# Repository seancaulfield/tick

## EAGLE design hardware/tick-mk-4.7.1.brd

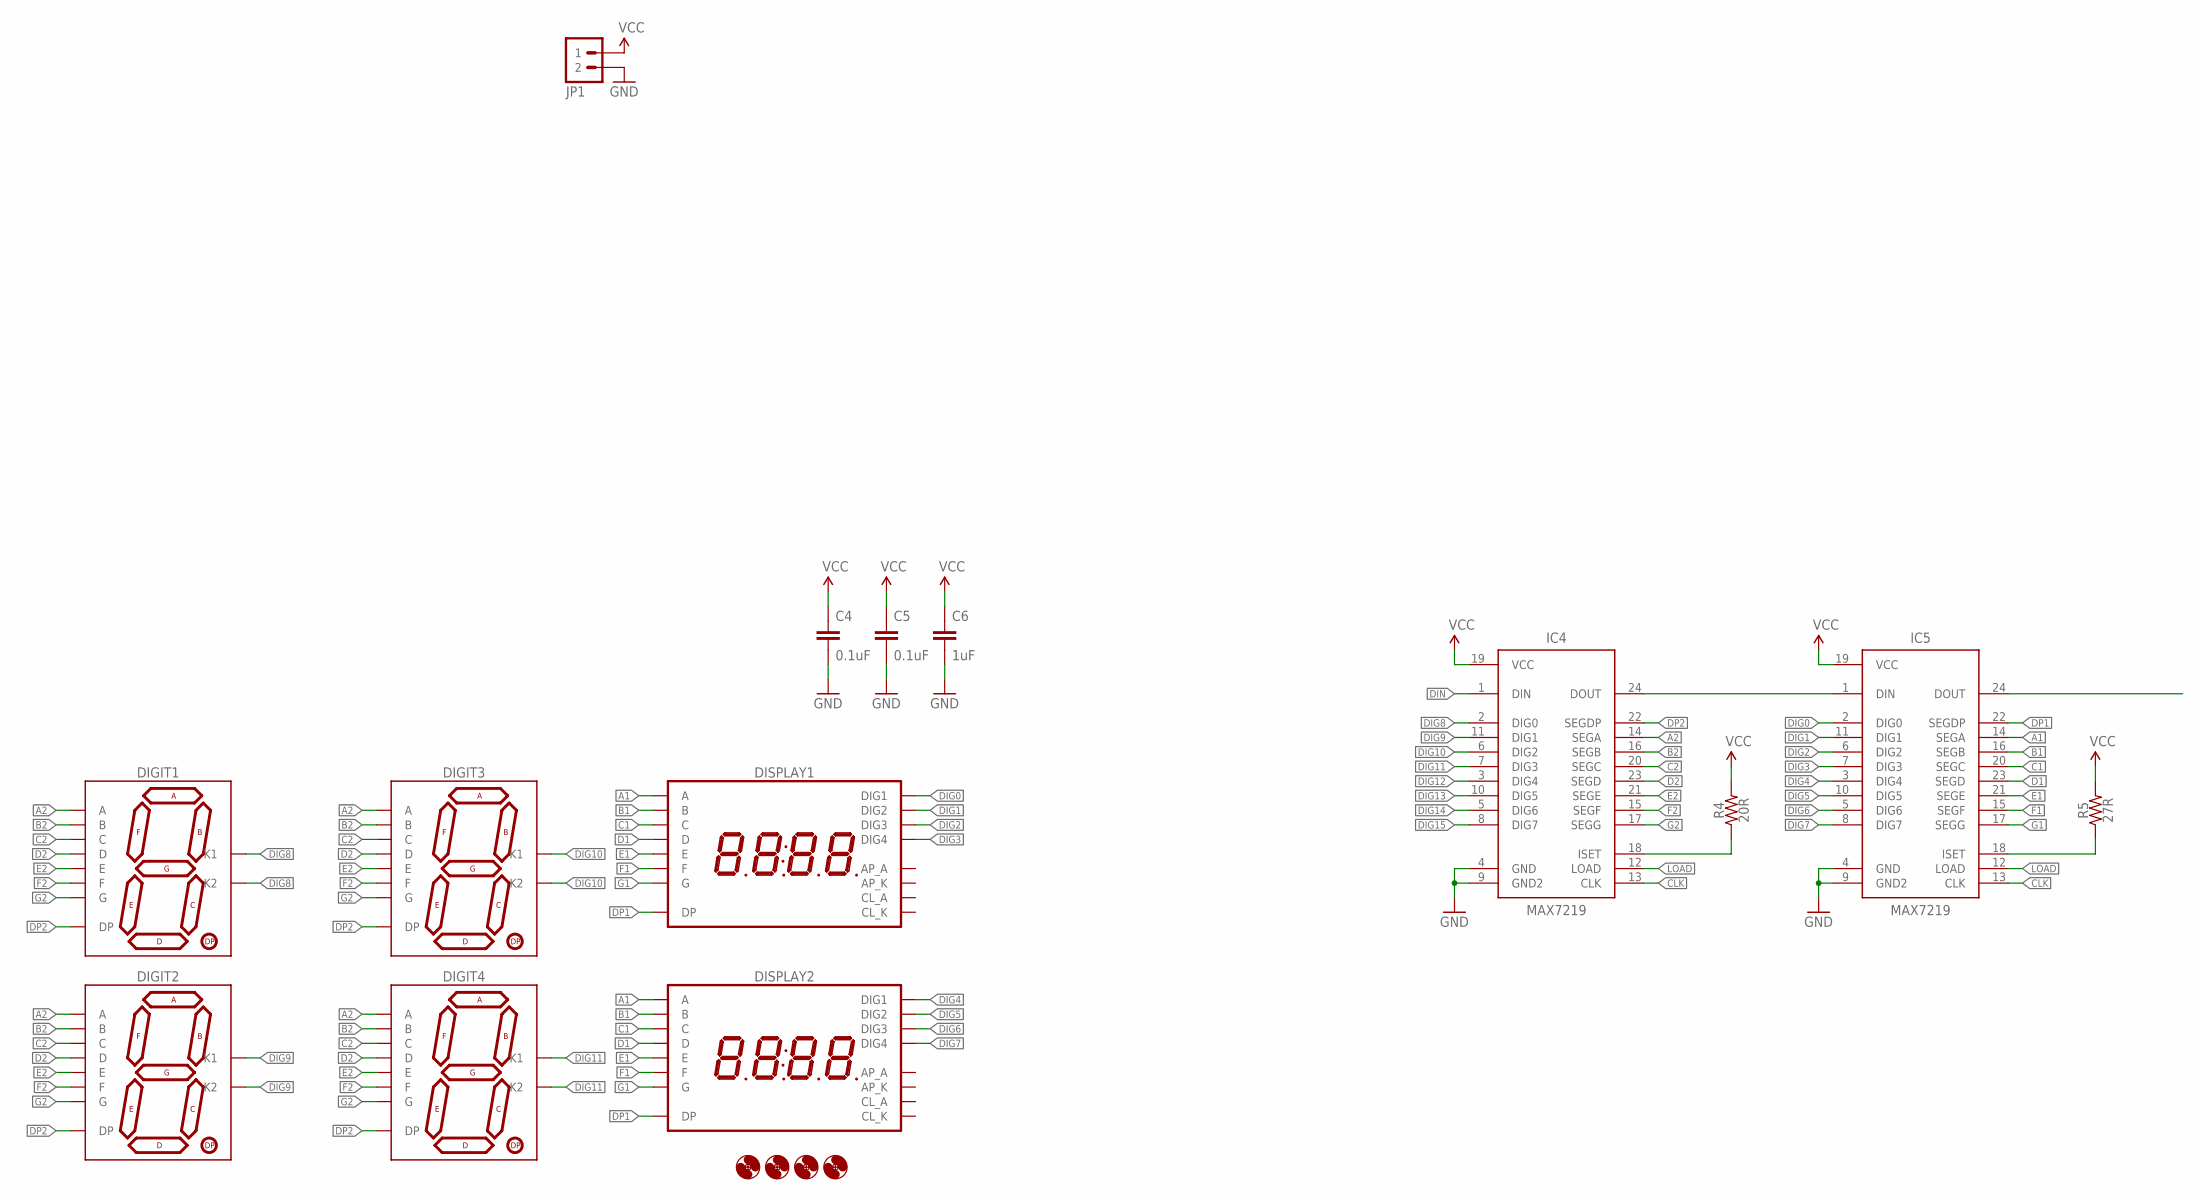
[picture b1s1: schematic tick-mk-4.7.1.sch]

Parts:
C4, C5: 0.1uF; C025-024X044
C6: 1uF; C025-024X044
DIGIT1, DIGIT2, DIGIT3, DIGIT4: 7SEG_1DIGPTH-25.4MM-BARE; 7SEG_1DIG_25.4MM_NOSILK
DISPLAY1, DISPLAY2: 7SEG_4DIGIT_COLON_APOS; 7SEG_4DIG_10MM
H1, H2, H3, H4: HOLE#2; HOLE-#2
IC4, IC5: MAX7219; SO24W
JP1: M02JST-XH-VERT; JST-2-XH-VERT-PTH
R4: 20R; RESISTOR-AXIAL-PTH-7.62MM
R5: 27R; RESISTOR-AXIAL-PTH-7.62MM

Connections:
A1: DISPLAY1.14 (A), DISPLAY2.14 (A), IC5.14 (SEGA)
A2: DIGIT1.7 (A), DIGIT2.7 (A), DIGIT3.7 (A), DIGIT4.7 (A), IC4.14 (SEGA)
B1: DISPLAY1.16 (B), DISPLAY2.16 (B), IC5.16 (SEGB)
B2: DIGIT1.6 (B), DIGIT2.6 (B), DIGIT3.6 (B), DIGIT4.6 (B), IC4.16 (SEGB)
C1: DISPLAY1.13 (C), DISPLAY2.13 (C), IC5.20 (SEGC)
C2: DIGIT1.4 (C), DIGIT2.4 (C), DIGIT3.4 (C), DIGIT4.4 (C), IC4.20 (SEGC)
CLK: IC4.13 (CLK), IC5.13 (CLK)
D1: DISPLAY1.3 (D), DISPLAY2.3 (D), IC5.23 (SEGD)
D2: DIGIT1.2 (D), DIGIT2.2 (D), DIGIT3.2 (D), DIGIT4.2 (D), IC4.23 (SEGD)
DIG0: DISPLAY1.1 (DIG1), IC5.2 (DIG0)
DIG1: DISPLAY1.2 (DIG2), IC5.11 (DIG1)
DIG2: DISPLAY1.6 (DIG3), IC5.6 (DIG2)
DIG3: DISPLAY1.8 (DIG4), IC5.7 (DIG3)
DIG4: DISPLAY2.1 (DIG1), IC5.3 (DIG4)
DIG5: DISPLAY2.2 (DIG2), IC5.10 (DIG5)
DIG6: DISPLAY2.6 (DIG3), IC5.5 (DIG6)
DIG7: DISPLAY2.8 (DIG4), IC5.8 (DIG7)
DIG8: DIGIT1.3 (K1), DIGIT1.8 (K2), IC4.2 (DIG0)
DIG9: DIGIT2.3 (K1), DIGIT2.8 (K2), IC4.11 (DIG1)
DIG10: DIGIT3.3 (K1), DIGIT3.8 (K2), IC4.6 (DIG2)
DIG11: DIGIT4.3 (K1), DIGIT4.8 (K2), IC4.7 (DIG3)
DIG12: IC4.3 (DIG4)
DIG13: IC4.10 (DIG5)
DIG14: IC4.5 (DIG6)
DIG15: IC4.8 (DIG7)
DIN: IC4.1 (DIN)
DOUT: IC4.24 (DOUT), IC5.1 (DIN)
DP1: DISPLAY1.7 (DP), DISPLAY2.7 (DP), IC5.22 (SEGDP)
DP2: DIGIT1.5 (DP), DIGIT2.5 (DP), DIGIT3.5 (DP), DIGIT4.5 (DP), IC4.22 (SEGDP)
E1: DISPLAY1.5 (E), DISPLAY2.5 (E), IC5.21 (SEGE)
E2: DIGIT1.1 (E), DIGIT2.1 (E), DIGIT3.1 (E), DIGIT4.1 (E), IC4.21 (SEGE)
F1: DISPLAY1.11 (F), DISPLAY2.11 (F), IC5.15 (SEGF)
F2: DIGIT1.9 (F), DIGIT2.9 (F), DIGIT3.9 (F), DIGIT4.9 (F), IC4.15 (SEGF)
G1: DISPLAY1.15 (G), DISPLAY2.15 (G), IC5.17 (SEGG)
G2: DIGIT1.10 (G), DIGIT2.10 (G), DIGIT3.10 (G), DIGIT4.10 (G), IC4.17 (SEGG)
GND: C4.2, C5.2, C6.2, IC4.4 (GND), IC4.9 (GND2), IC5.4 (GND), IC5.9 (GND2), JP1.2
LOAD: IC4.12 (LOAD), IC5.12 (LOAD)
unnamed: IC5.18 (ISET), R5.P$1 (1)
unnamed: IC4.18 (ISET), R4.P$1 (1)
VCC: C4.1, C5.1, C6.1, IC4.19 (VCC), IC5.19 (VCC), JP1.1, R4.P$2 (2), R5.P$2 (2)

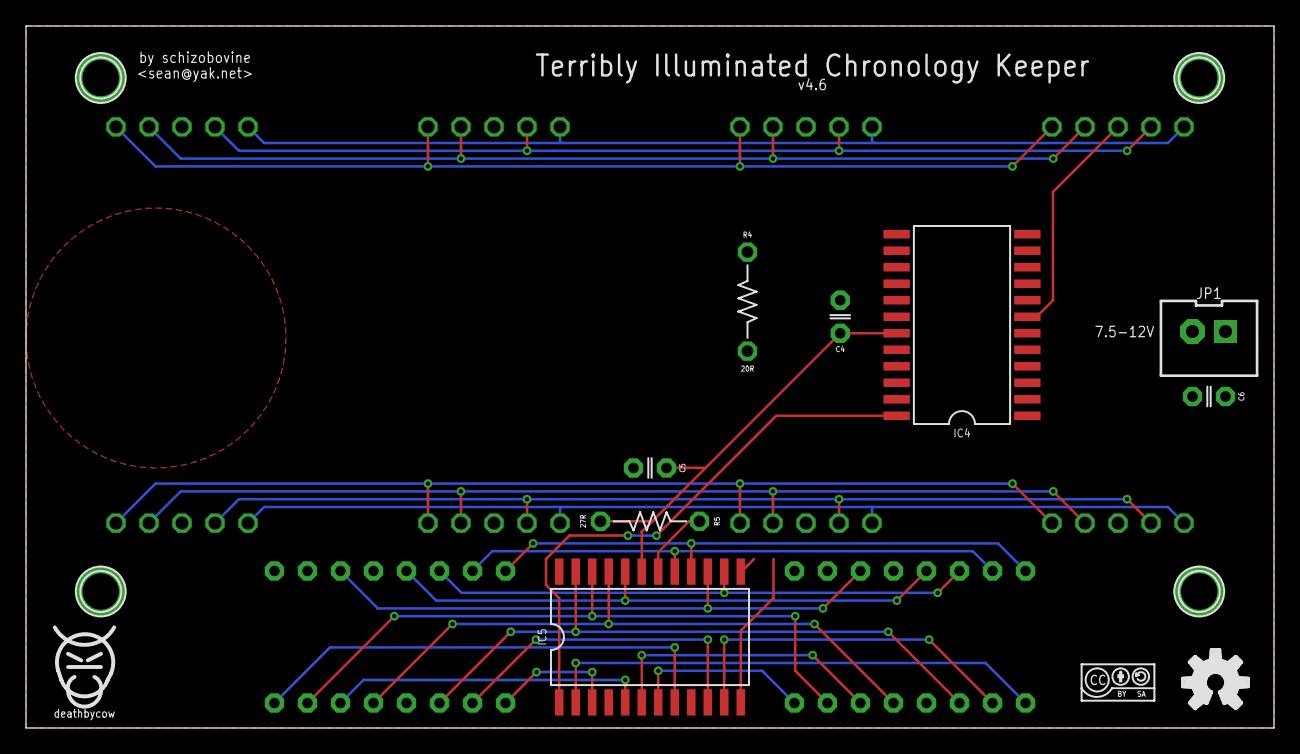
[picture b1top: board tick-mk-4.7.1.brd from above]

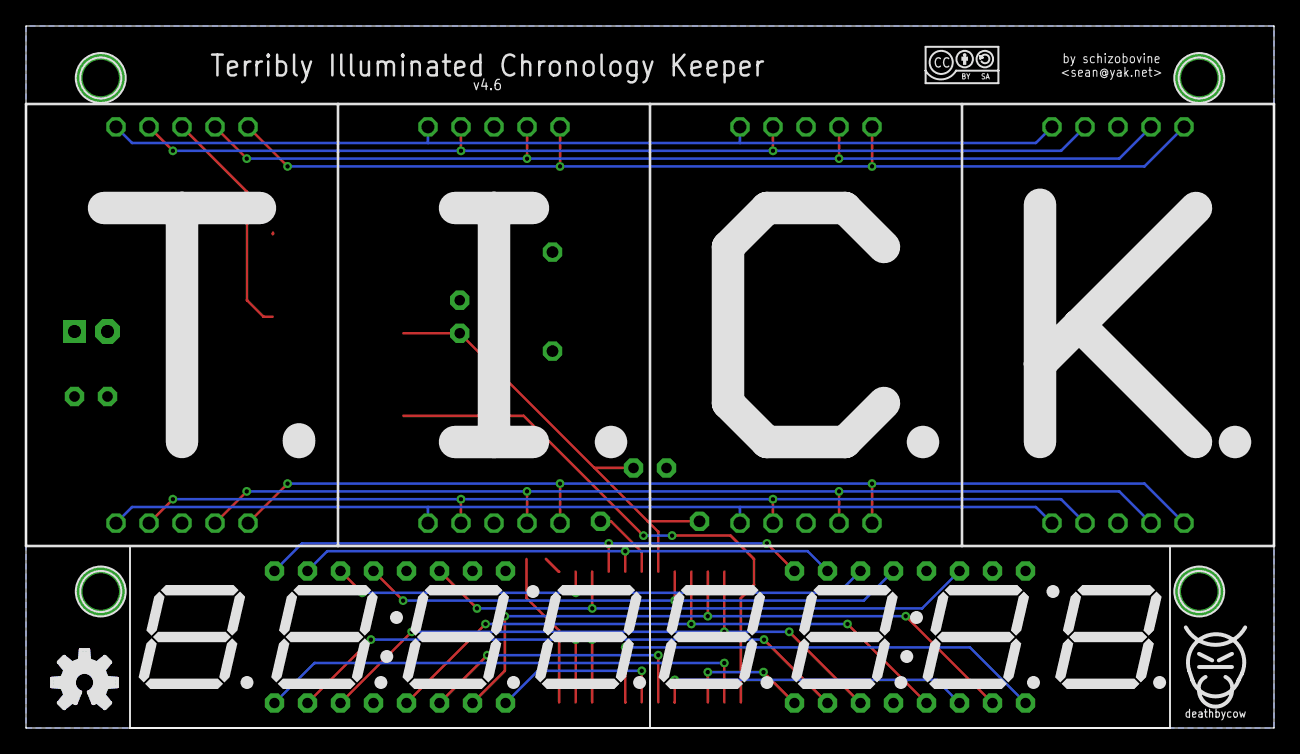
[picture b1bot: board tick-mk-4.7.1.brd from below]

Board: 2 copper layers, 96.0 x 54.0 mm, 24 parts (9 on the bottom side), 35 nets.

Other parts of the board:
U$1, U$4: COW_SMALL
U$2, U$3: CC-BY-SA-4.0-NO-URL
U$5, U$8: OSHWLOGO_TOP_0.2

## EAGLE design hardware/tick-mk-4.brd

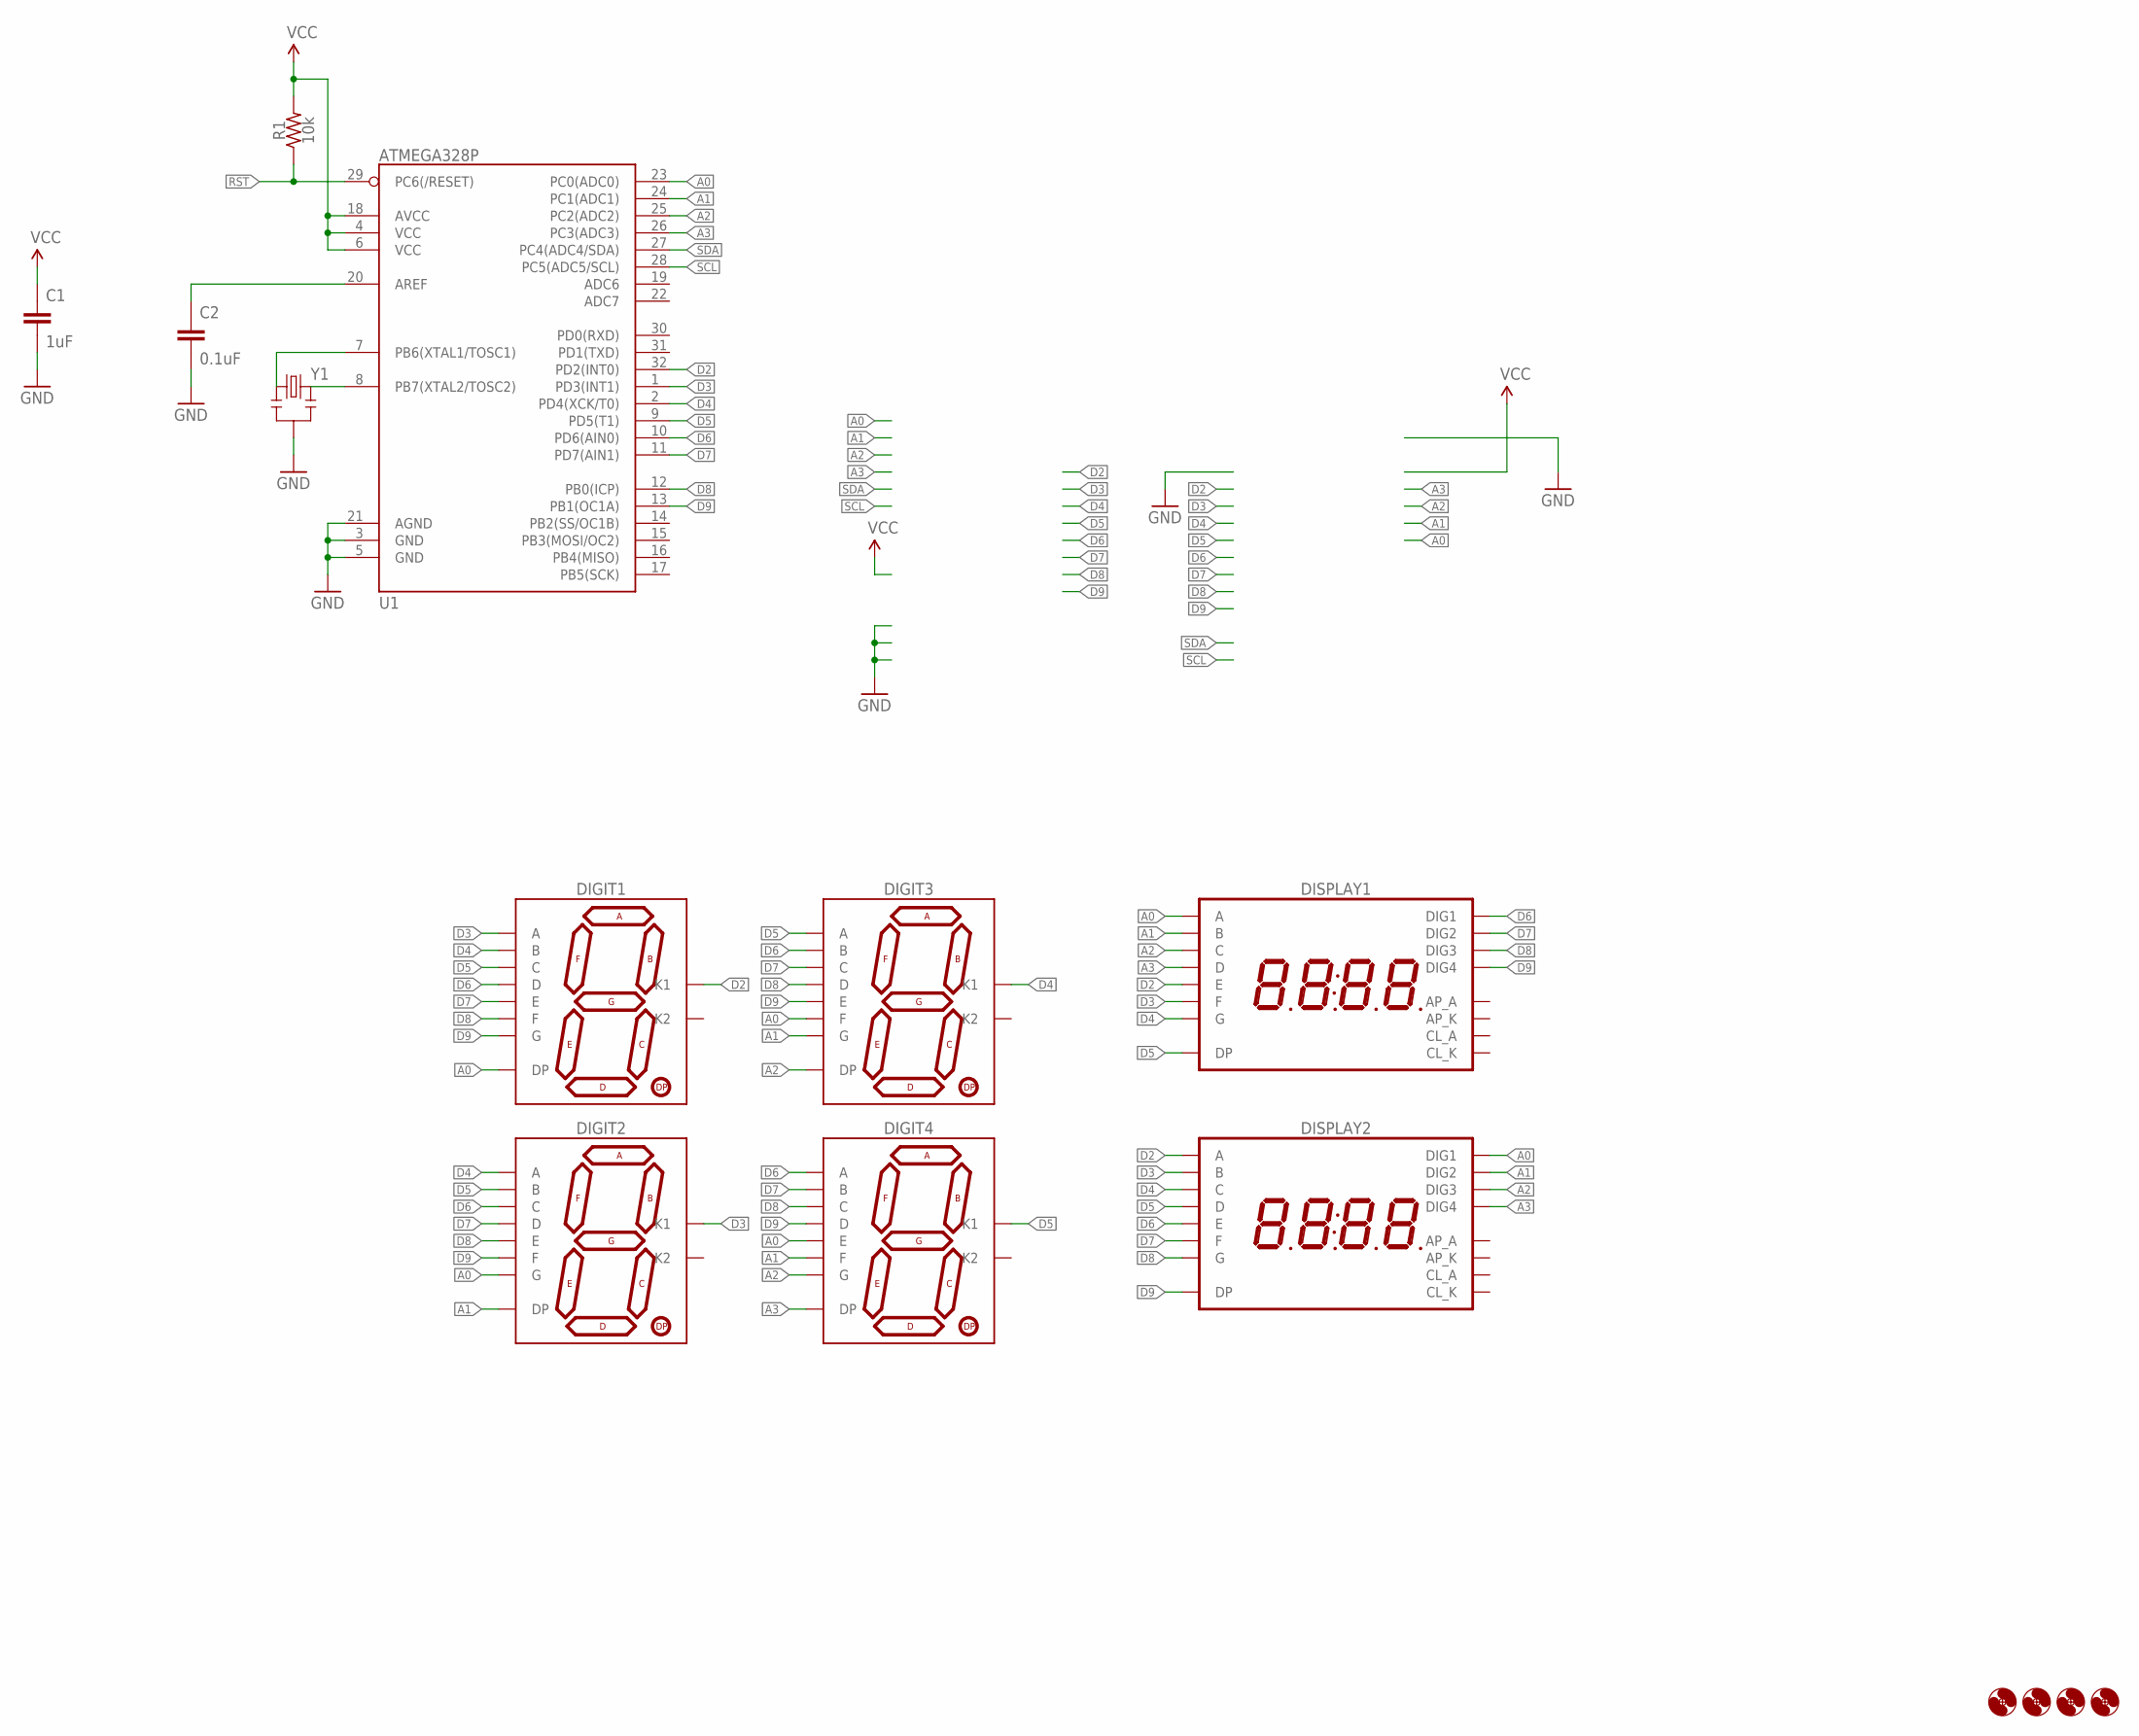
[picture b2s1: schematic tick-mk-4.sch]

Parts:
C1: 1uF; C0805
C2: 0.1uF; C0805
DIGIT1, DIGIT2, DIGIT3, DIGIT4: 7SEG_1DIGPTH-25.4MM; 7SEG_1DIG_25.4MM
DISPLAY1, DISPLAY2: 7SEG_4DIGIT_COLON_APOS; 7SEG_4DIG_10MM
H1, H2, H3, H4: HOLE#2; HOLE-#2
R1: 10k; R0805
U1: ATMEGA328P; TQFP32-08
Y1: RESONATORSMD-4.7X4.1X1.2; RESONATOR-4.7X4.1X1.2MM

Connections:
A0: DIGIT1.5 (DP), DIGIT2.10 (G), DIGIT3.9 (F), DIGIT4.1 (E), DISPLAY1.14 (A), DISPLAY2.1 (DIG1), U1.23 (PC0(ADC0))
A1: DIGIT2.5 (DP), DIGIT3.10 (G), DIGIT4.9 (F), DISPLAY1.16 (B), DISPLAY2.2 (DIG2), U1.24 (PC1(ADC1))
A2: DIGIT3.5 (DP), DIGIT4.10 (G), DISPLAY1.13 (C), DISPLAY2.6 (DIG3), U1.25 (PC2(ADC2))
A3: DIGIT4.5 (DP), DISPLAY1.3 (D), DISPLAY2.8 (DIG4), U1.26 (PC3(ADC3))
D2: DIGIT1.3 (K1), DISPLAY1.5 (E), DISPLAY2.14 (A), U1.32 (PD2(INT0))
D3: DIGIT1.7 (A), DIGIT2.3 (K1), DISPLAY1.11 (F), DISPLAY2.16 (B), U1.1 (PD3(INT1))
D4: DIGIT1.6 (B), DIGIT2.7 (A), DIGIT3.3 (K1), DISPLAY1.15 (G), DISPLAY2.13 (C), U1.2 (PD4(XCK/T0))
D5: DIGIT1.4 (C), DIGIT2.6 (B), DIGIT3.7 (A), DIGIT4.3 (K1), DISPLAY1.7 (DP), DISPLAY2.3 (D), U1.9 (PD5(T1))
D6: DIGIT1.2 (D), DIGIT2.4 (C), DIGIT3.6 (B), DIGIT4.7 (A), DISPLAY1.1 (DIG1), DISPLAY2.5 (E), U1.10 (PD6(AIN0))
D7: DIGIT1.1 (E), DIGIT2.2 (D), DIGIT3.4 (C), DIGIT4.6 (B), DISPLAY1.2 (DIG2), DISPLAY2.11 (F), U1.11 (PD7(AIN1))
D8: DIGIT1.9 (F), DIGIT2.1 (E), DIGIT3.2 (D), DIGIT4.4 (C), DISPLAY1.6 (DIG3), DISPLAY2.15 (G), U1.12 (PB0(ICP))
D9: DIGIT1.10 (G), DIGIT2.9 (F), DIGIT3.1 (E), DIGIT4.2 (D), DISPLAY1.8 (DIG4), DISPLAY2.7 (DP), U1.13 (PB1(OC1A))
GND: C1.2, C2.2, U1.3 (GND), U1.5 (GND), U1.21 (AGND), Y1.2
unnamed: C2.1, U1.20 (AREF)
unnamed: U1.7 (PB6(XTAL1/TOSC1)), Y1.1
unnamed: U1.8 (PB7(XTAL2/TOSC2)), Y1.3
RST: R1.1, U1.29 (PC6(/RESET))
SCL: U1.28 (PC5(ADC5/SCL))
SDA: U1.27 (PC4(ADC4/SDA))
VCC: C1.1, R1.2, U1.4 (VCC), U1.6 (VCC), U1.18 (AVCC)

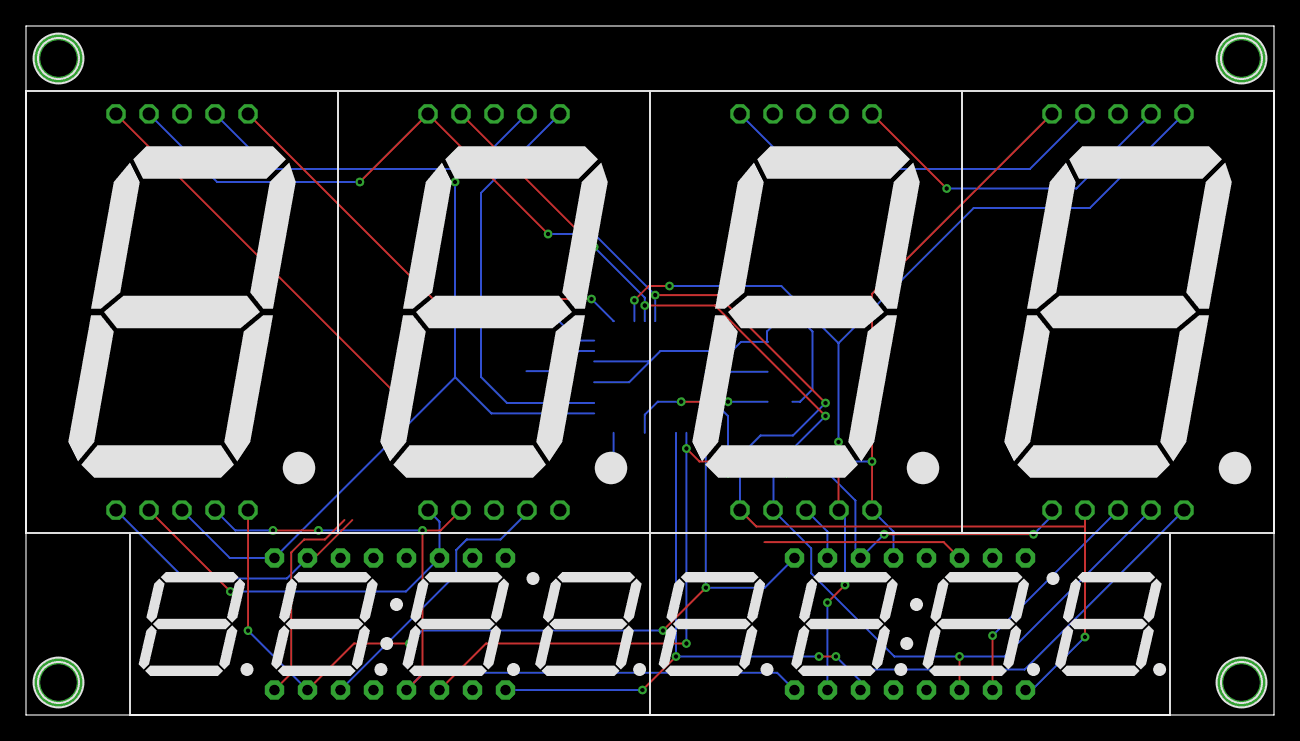
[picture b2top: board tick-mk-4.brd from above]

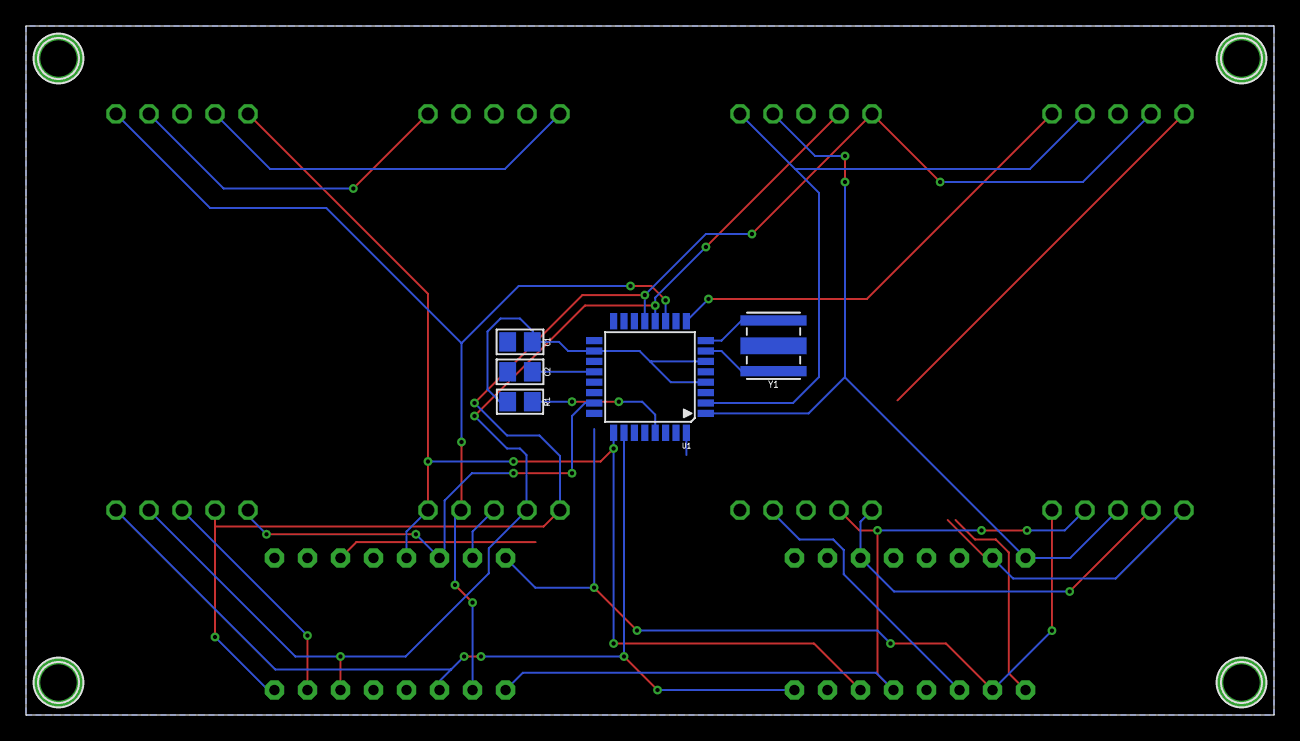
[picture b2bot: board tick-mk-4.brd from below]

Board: 2 copper layers, 96.0 x 53.0 mm, 15 parts (5 on the bottom side), 18 nets.

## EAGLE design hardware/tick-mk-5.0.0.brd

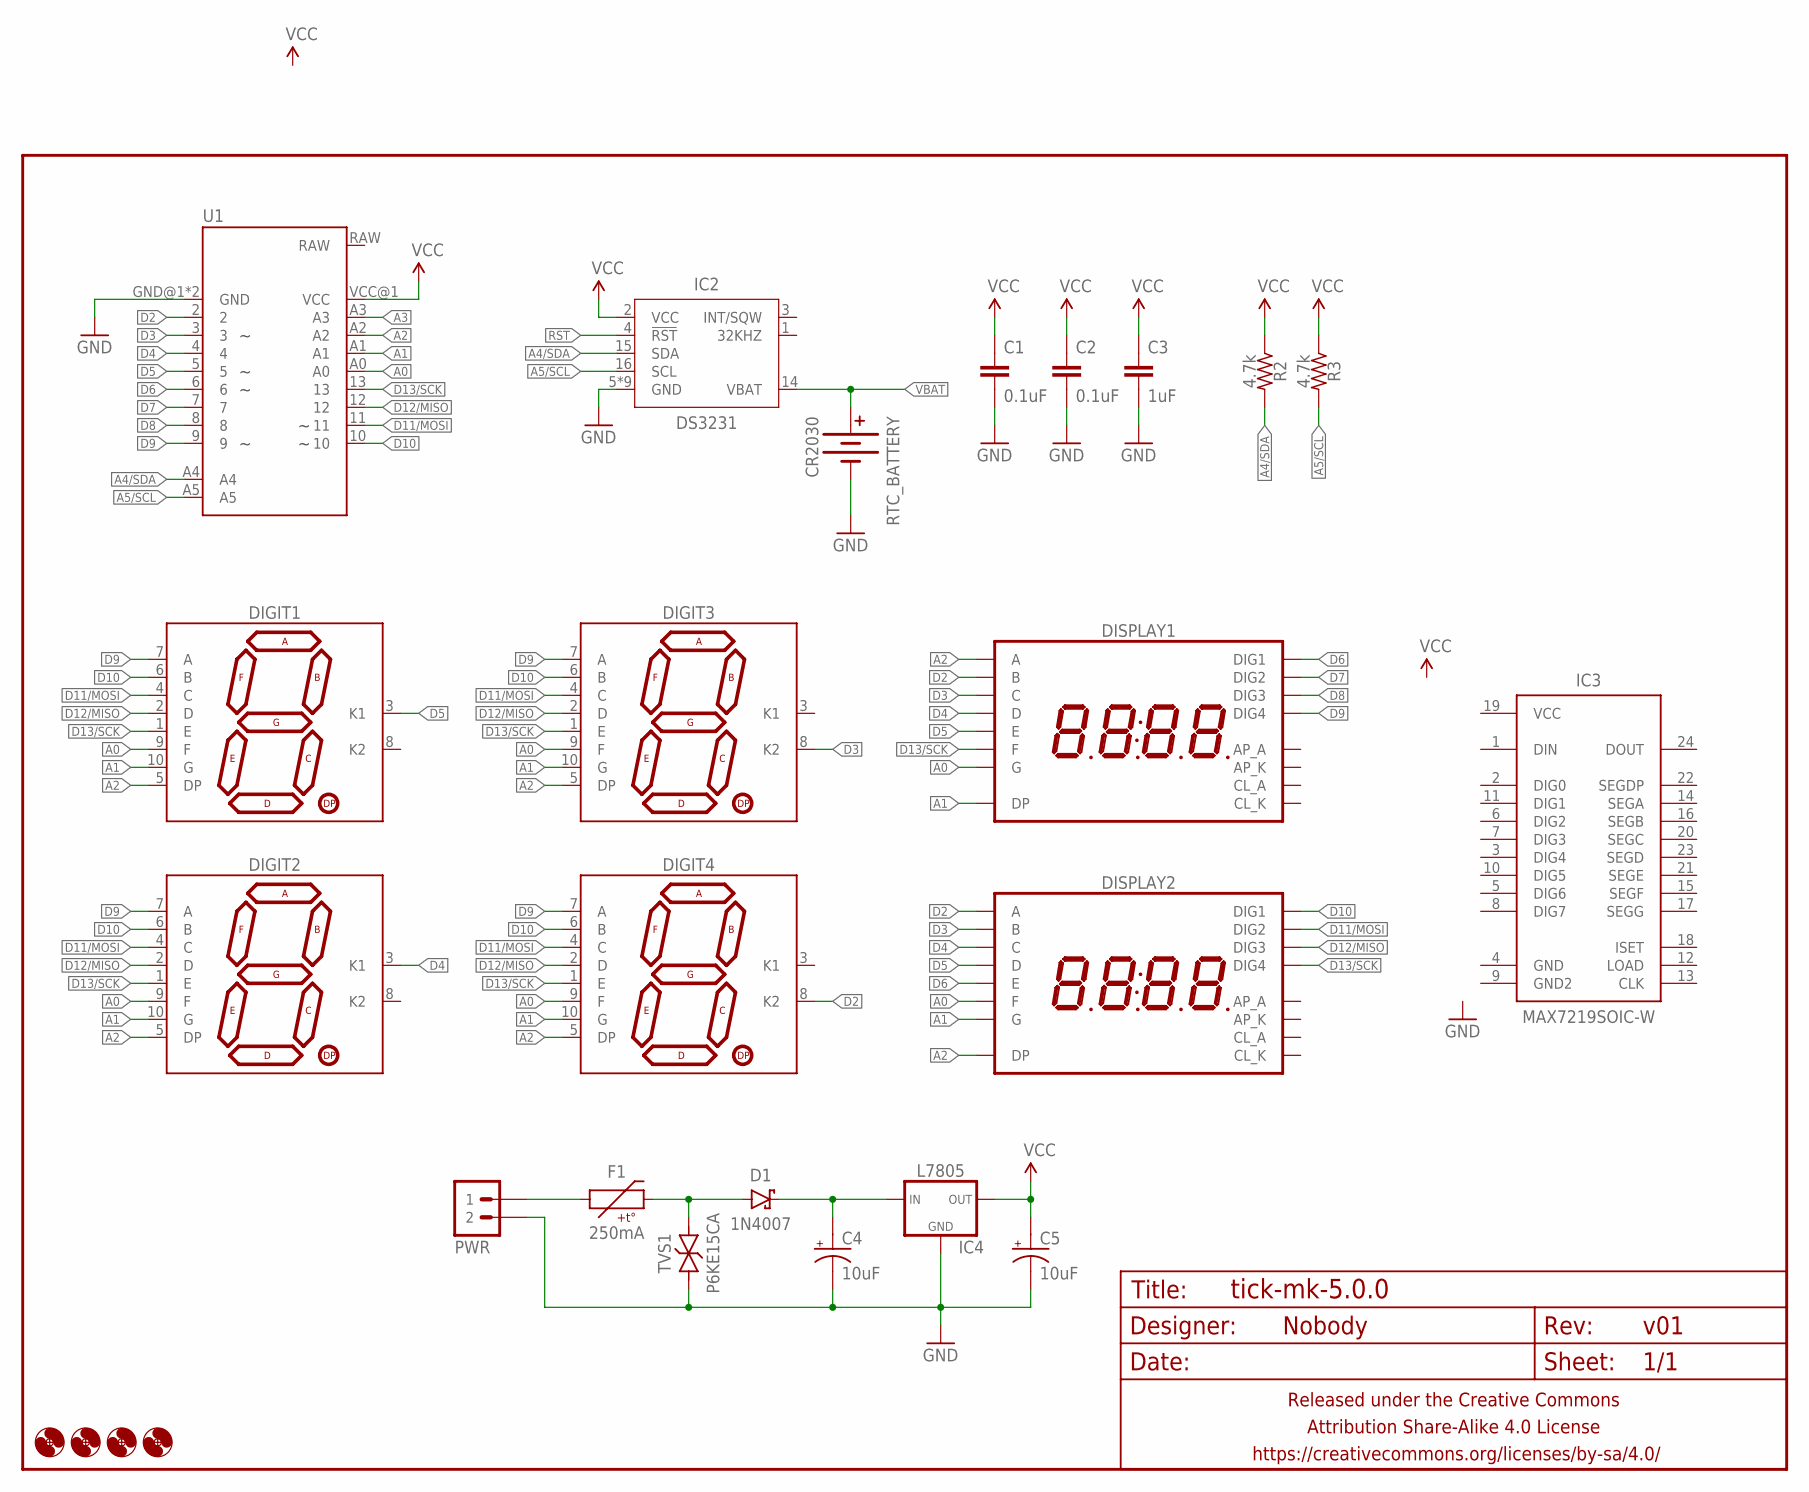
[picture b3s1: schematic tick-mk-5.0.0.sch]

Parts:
C1, C2: 0.1uF; C025-024X044
C3: 1uF; C025-024X044
C4, C5: 10uF; E2-5
D1: 1N4007; DIODE-10.16MM
DIGIT1, DIGIT2, DIGIT3, DIGIT4: 7SEG_1DIGPTH-25.4MM-BARE; 7SEG_1DIG_25.4MM_NOSILK
DISPLAY1, DISPLAY2: 7SEG_4DIGIT_COLON_APOS; 7SEG_4DIG_10MM
F1: 250mA; PTC-PTH-5.08MM
FRAME1: FRAME-LETTERNO_PACKAGE; DUMMY
H1, H2, H3, H4: HOLE2,5; 2,5
IC2: DS3231; SO16W
IC3: MAX7219SOIC-W; SO24W
IC4: L7805; TO220-IGO-THERMPAD
PWR: M02JST-PTH-VERT; JST-2-PH-VERT-PTH
R2, R3: 4.7k; RESISTOR-AXIAL-PTH-6.35MM
RTC_BATTERY: CR2030; BATTCON_20MM_MINE_STAHPIT
TVS1: P6KE15CA; DO-41-TVS-BI-10.16MM
U1: ARDUINO_PRO_MINI_TICK2

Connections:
A0: DIGIT1.9 (F), DIGIT2.9 (F), DIGIT3.9 (F), DIGIT4.9 (F), DISPLAY1.15 (G), DISPLAY2.11 (F), U1.A0
A1: DIGIT1.10 (G), DIGIT2.10 (G), DIGIT3.10 (G), DIGIT4.10 (G), DISPLAY1.7 (DP), DISPLAY2.15 (G), U1.A1
A2: DIGIT1.5 (DP), DIGIT2.5 (DP), DIGIT3.5 (DP), DIGIT4.5 (DP), DISPLAY1.14 (A), DISPLAY2.7 (DP), U1.A2
A3: U1.A3
A4/SDA: IC2.15 (SDA), R2.P$2 (2), U1.A4
A5/SCL: IC2.16 (SCL), R3.P$2 (2), U1.A5
D2: DIGIT4.8 (K2), DISPLAY1.16 (B), DISPLAY2.14 (A), U1.2
D3: DIGIT3.8 (K2), DISPLAY1.13 (C), DISPLAY2.16 (B), U1.3
D4: DIGIT2.3 (K1), DISPLAY1.3 (D), DISPLAY2.13 (C), U1.4
D5: DIGIT1.3 (K1), DISPLAY1.5 (E), DISPLAY2.3 (D), U1.5
D6: DISPLAY1.1 (DIG1), DISPLAY2.5 (E), U1.6
D7: DISPLAY1.2 (DIG2), U1.7
D8: DISPLAY1.6 (DIG3), U1.8
D9: DIGIT1.7 (A), DIGIT2.7 (A), DIGIT3.7 (A), DIGIT4.7 (A), DISPLAY1.8 (DIG4), U1.9
D10: DIGIT1.6 (B), DIGIT2.6 (B), DIGIT3.6 (B), DIGIT4.6 (B), DISPLAY2.1 (DIG1), U1.10
D11/MOSI: DIGIT1.4 (C), DIGIT2.4 (C), DIGIT3.4 (C), DIGIT4.4 (C), DISPLAY2.2 (DIG2), U1.11
D12/MISO: DIGIT1.2 (D), DIGIT2.2 (D), DIGIT3.2 (D), DIGIT4.2 (D), DISPLAY2.6 (DIG3), U1.12
D13/SCK: DIGIT1.1 (E), DIGIT2.1 (E), DIGIT3.1 (E), DIGIT4.1 (E), DISPLAY1.11 (F), DISPLAY2.8 (DIG4), U1.13
GND: C1.2, C2.2, C3.2, C4.-, C5.-, IC2.5 (GND), IC2.6 (GND), IC2.7 (GND), IC2.8 (GND), IC2.9 (GND), IC2.10 (GND), IC2.11 (GND), IC2.12 (GND), IC2.13 (GND), IC4.4 (GND), IC4.GND, PWR.2, RTC_BATTERY.BOTTOM (-), TVS1.P$1 (1), U1.GND@1 (GND), U1.GND@2 (GND)
unnamed: D1.A, F1.P$2 (2), TVS1.P$2 (2)
unnamed: F1.P$1 (1), PWR.1
unnamed: C4.+, D1.C, IC4.IN
RST: IC2.4 (!RST)
VBAT: IC2.14 (VBAT), RTC_BATTERY.TOP@1 (+), RTC_BATTERY.TOP@2 (+)
VCC: C1.1, C2.1, C3.1, C5.+, IC2.2 (VCC), IC4.OUT, R2.P$1 (1), R3.P$1 (1), U1.VCC@1 (VCC)

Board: 2 copper layers, 28 parts (7 on the bottom side), 23 nets, no tracks yet.

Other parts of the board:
U$1: TICK_SYMBOL

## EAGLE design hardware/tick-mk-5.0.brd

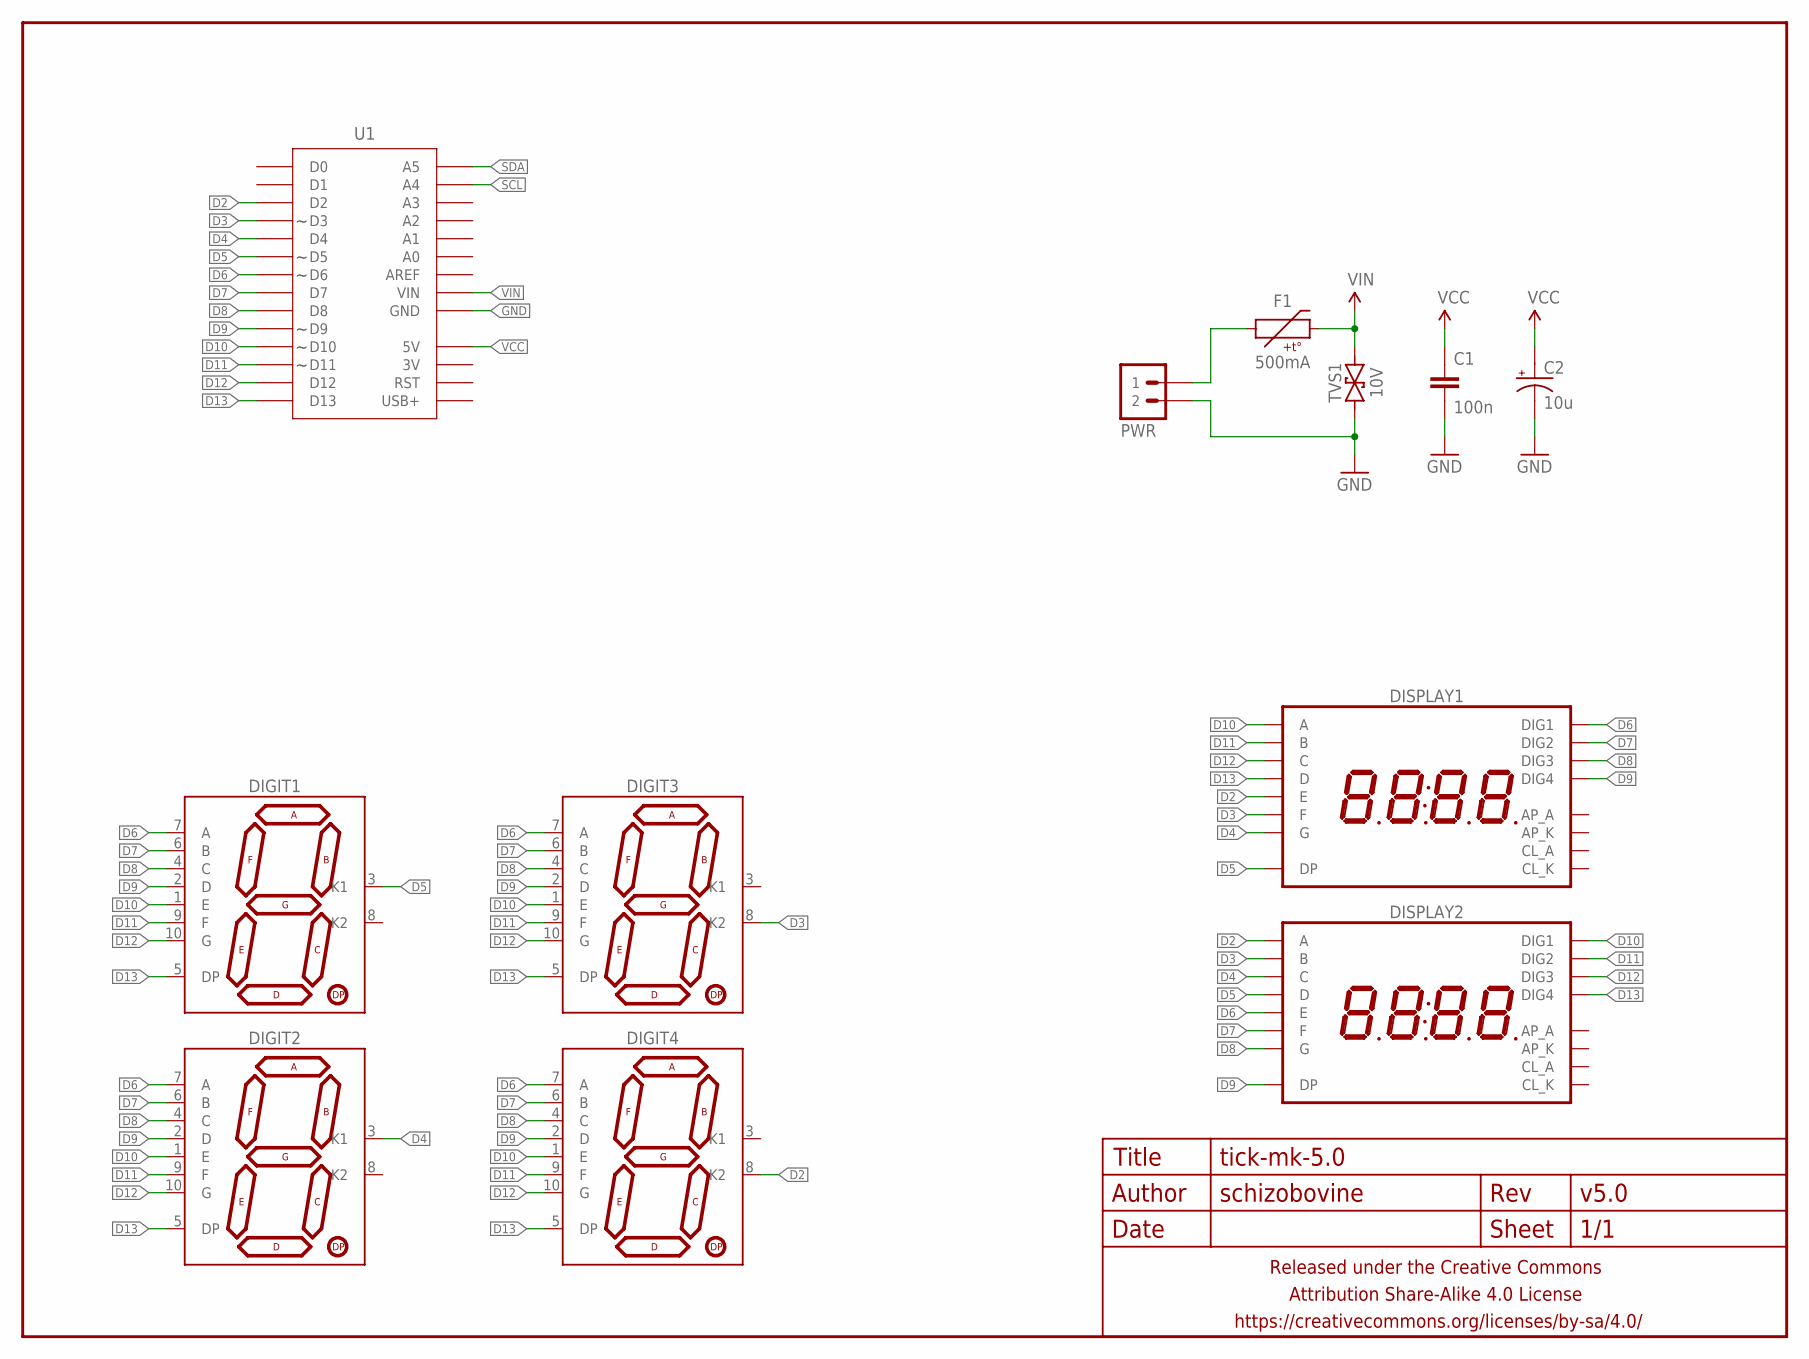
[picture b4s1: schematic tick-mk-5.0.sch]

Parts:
C1: 100n; C025-024X044
C2: 10u; E2-5
DIGIT1, DIGIT2, DIGIT3, DIGIT4: 7SEG_1DIGPTH-25.4MM-BARE; 7SEG_1DIG_25.4MM_NOSILK
DISPLAY1, DISPLAY2: 7SEG_4DIGIT_COLON_APOS; 7SEG_4DIG_10MM
F1: 500mA; PTC-PTH-5.08MM
FRAME1: FRAME-LETTERNO_PACKAGE; DUMMY
PWR: M02JST-PTH-VERT; JST-2-PH-VERT-PTH
TVS1: 10V; DO-41-TVS-BI-10.16MM
U1: ADAFRUIT_METRO_MININOHOLES-NOOUTLINE-SILK; ADAFRUIT_METRO_MINI

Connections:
D2: DIGIT4.8 (K2), DISPLAY1.5 (E), DISPLAY2.14 (A), U1.3 (D2)
D3: DIGIT3.8 (K2), DISPLAY1.11 (F), DISPLAY2.16 (B), U1.4 (D3)
D4: DIGIT2.3 (K1), DISPLAY1.15 (G), DISPLAY2.13 (C), U1.5 (D4)
D5: DIGIT1.3 (K1), DISPLAY1.7 (DP), DISPLAY2.3 (D), U1.6 (D5)
D6: DIGIT1.7 (A), DIGIT2.7 (A), DIGIT3.7 (A), DIGIT4.7 (A), DISPLAY1.1 (DIG1), DISPLAY2.5 (E), U1.7 (D6)
D7: DIGIT1.6 (B), DIGIT2.6 (B), DIGIT3.6 (B), DIGIT4.6 (B), DISPLAY1.2 (DIG2), DISPLAY2.11 (F), U1.8 (D7)
D8: DIGIT1.4 (C), DIGIT2.4 (C), DIGIT3.4 (C), DIGIT4.4 (C), DISPLAY1.6 (DIG3), DISPLAY2.15 (G), U1.9 (D8)
D9: DIGIT1.2 (D), DIGIT2.2 (D), DIGIT3.2 (D), DIGIT4.2 (D), DISPLAY1.8 (DIG4), DISPLAY2.7 (DP), U1.10 (D9)
D10: DIGIT1.1 (E), DIGIT2.1 (E), DIGIT3.1 (E), DIGIT4.1 (E), DISPLAY1.14 (A), DISPLAY2.1 (DIG1), U1.11 (D10)
D11: DIGIT1.9 (F), DIGIT2.9 (F), DIGIT3.9 (F), DIGIT4.9 (F), DISPLAY1.16 (B), DISPLAY2.2 (DIG2), U1.12 (D11)
D12: DIGIT1.10 (G), DIGIT2.10 (G), DIGIT3.10 (G), DIGIT4.10 (G), DISPLAY1.13 (C), DISPLAY2.6 (DIG3), U1.13 (D12)
D13: DIGIT1.5 (DP), DIGIT2.5 (DP), DIGIT3.5 (DP), DIGIT4.5 (DP), DISPLAY1.3 (D), DISPLAY2.8 (DIG4), U1.14 (D13)
GND: C1.2, C2.-, PWR.2, TVS1.P$1 (1), U1.19 (GND), U1.20 (GND)
unnamed: F1.P$1 (1), PWR.1
SCL: U1.27 (A4)
SDA: U1.28 (A5)
VCC: C1.1, C2.+, U1.18 (5V)
VIN: F1.P$2 (2), TVS1.P$2 (2), U1.21 (VIN)

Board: 2 copper layers, 19 parts (9 on the bottom side), 16 nets, no tracks yet.

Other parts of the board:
U$1: TICK_SYMBOL
U$2: COW_SMALL
U$4, U$7: CC-BY-SA-4.0-NO-URL
U$5, U$6: OSHWLOGO_TOP_0.2

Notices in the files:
parts and their libraries:
A_butts: Released under the Creative Commons Attribution Share-Alike 4.0 License
A_butts: https://creativecommons.org/licenses/by-sa/4.0
A_butts: Released under the Creative Commons
